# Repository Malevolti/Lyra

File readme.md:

*// Ingrediants //*

## Available from Mechboards ##
Pro-micro derivative x2 (except nice!nano right now) PUCHI-c or Elite-C Recommended (onboard reset switch)
0,91 oled x2
Trrs jacks x2- narrow (corne,lily style etc)
10 or 12mm standoffs x50
6mm M2 screws x100 (yeah I know...)
through hole diodes x70 (though buy 100)

## Elsewhere ##
Insulation tape
Hookup wire
Brass or Copper rods 1-3mm width (This is optional but saves some time using in place of hookup wire on the collumns)

Case & plates - I can print these for you on demand, I'm going to release them open source eventually so can give you the stls if you have access to a printer or someone closer to you than me

*// Main build instructions //*

Google QMK - Handwire for the general instructions on how to handwire but a brief overview is:

1. Solder a diode to one  switch pin in direction marked below; other end soldered to the row "bus"; you can use the diode legs to from the row bus as long as the diode module is in parallel to the row bus.
2. Solder hookup wire or brass/copper rod to the other switch pin in direction marked below to form the collumn "bus"; no special considarations needed other than to insulate the collumns from the rows, especially if you are using a bare brass/copper rod; this is where the insulation tape comes in.

           ^ = Collumn bus
           |
<-----+----------> = Row bus
      _    |
Diode=^    |
      | O  o = Switch pins
      o    |
           |
           v

3. Once you have completed the matrix (above and below) then hook the collumn and row busses to the controller using the below diagram for reference; you can hook up each collumn or row at any point along each.

Matrix & pro micro pinout:

Left side - flipped over-

    0-F4 1-F5 2-F6 3-F7 4-B1 5-B3 6-B2
0-D4 +----+----+----+----+----+----+
     |    |    |    |    |    |    |
1-C6 +----+----+----+----+----+----+
     |    |    |    |    |    |    |
2-D7 +----+----+----+----+----+----+
     |    |    |    |    |    |    |
3-E6 +----+----+----+----+----+----+
     |    |    |    |    |    |    |
4-B5 +----+----+----+----+----+----+

Right side - flipped over-

    6-B2 5-B3 4-B1 3-F7 2-F6 1-F5 0-F4
0-D4 +----+----+----+----+----+----+
     |    |    |    |    |    |    |
1-C6 +----+----+----+----+----+----+
     |    |    |    |    |    |    |
2-D7 +----+----+----+----+----+----+
     |    |    |    |    |    |    |
3-E6 +----+----+----+----+----+----+
     |    |    |    |    |    |    |
4-B5 +----+----+----+----+----+----+

4. Wiring up the OLED -
	This is as simple as matching the pins named on the OLED module with the pins of the same name on the microcontroller; the main thing to know however is that the OLED shares the VCC in with the TRRS jack; I normally strip a small section of insulation from the wire between the oled VCC & MCU VCC and then soldering the Trrs vcc onto that as the hole on the mcu can only take one wire. Alternatively you can wire the oled vcc to the trrs pin that you choose to use for vcc and then wire the TRRS to the vcc on the mcu.

5. Wiring up the TRRS - 
	Normally the easiest part of soldering a split pcb; sadly this is a little bit fiddly with the lyra.
	Ignoring the pin on the TRRS that sits alone from the other three, it doesnt matter which pins you use for each pin on the microcontroller as long as you use the same ones on each trrs jack. 
	The three pins on the microcontroller needed for the TRRS are RX(D2), GND(any) & VCC (See above for info on shared use with 
	I would recommend using longer lengths of wire than appears needed due to how close the TRRS jacks are to the required pins.

------

*// Firmware //*
[Coming soon]

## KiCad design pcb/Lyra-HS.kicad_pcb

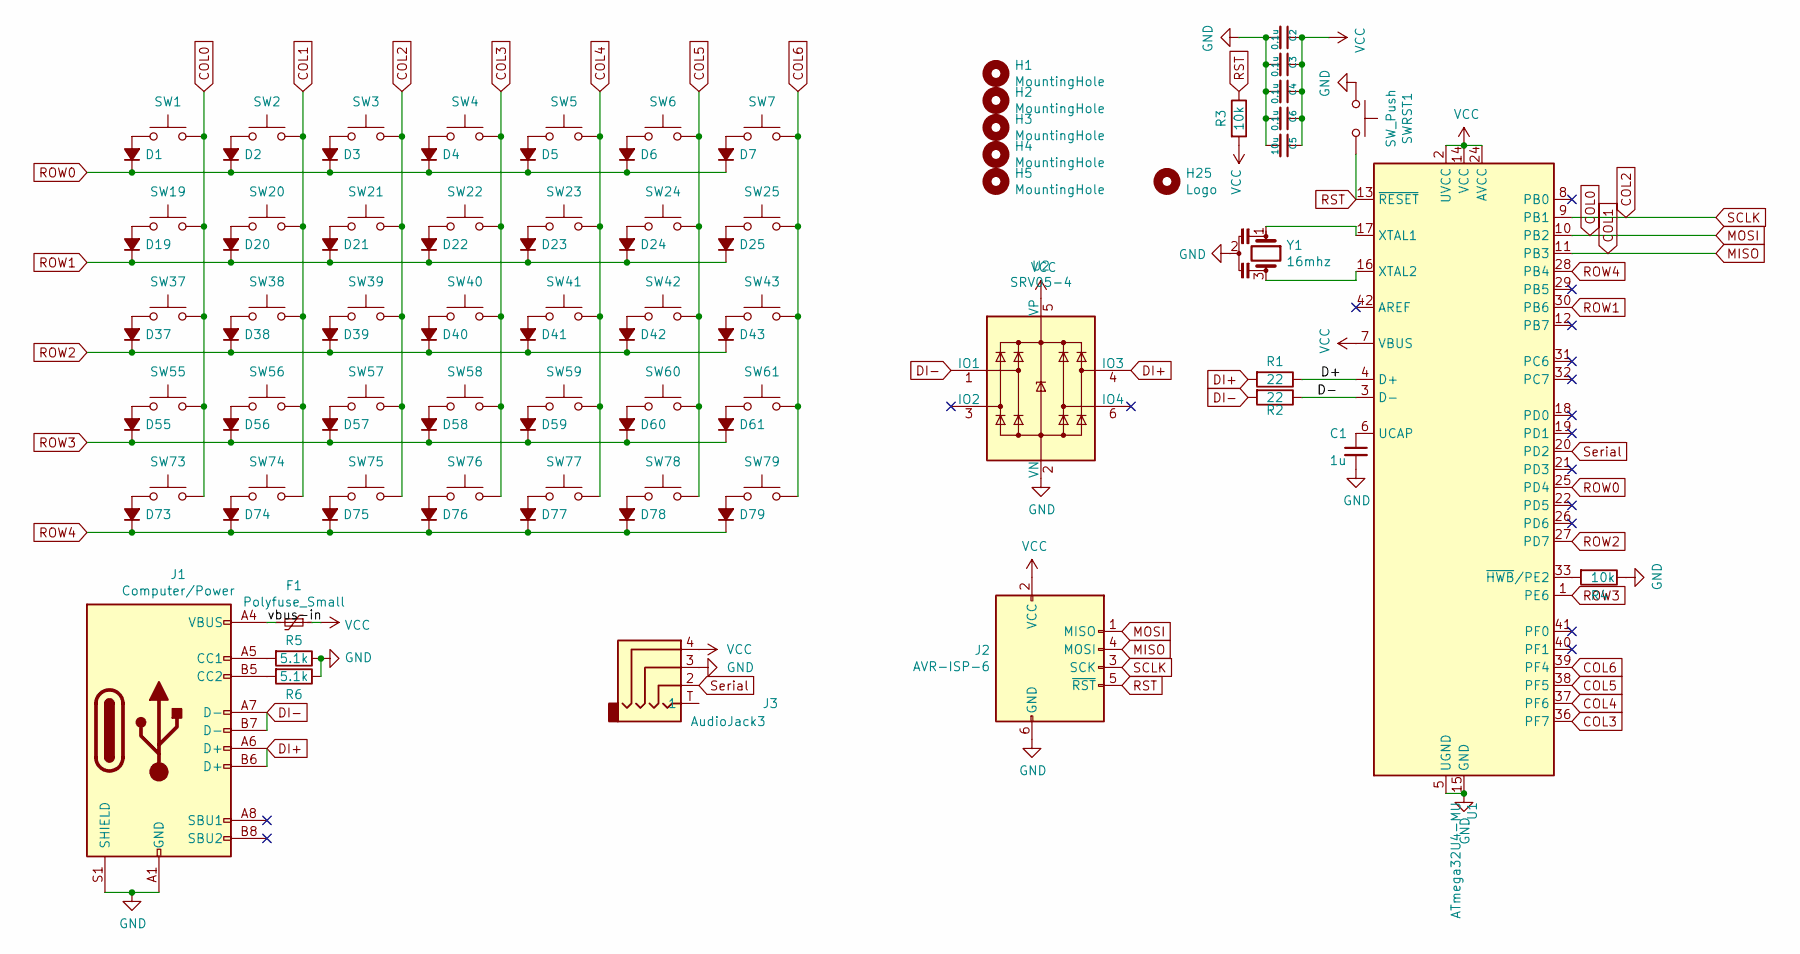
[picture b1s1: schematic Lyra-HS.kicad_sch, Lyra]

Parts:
C1: 1u; C_0402; LCSC C106253
C2, C3, C4, C6: 0.1u; C_0402; LCSC C106204
C5: 10u; C_0402; LCSC C237279
D1, D2, D3, D4, D5, D6, D7, D19, D20, D21, D22, D23, D24, D25, D37, D38, D39, D40, D41, D42, D43, D55, D56, D57, D58, D59, D60, D61, D73, D74, D75, D76, D77, D78, D79: D_Small_ALT; D_SOD-123F; LCSC C2099
F1: Polyfuse_Small; Fuse_0402_1005Metric; LCSC C914085
H1, H2, H3, H4, H5: MountingHole; MountingHole_2.2mm_M2_ISO7380_Pad
H25: Logo; SuperLyraLogo
J1: Computer/Power; USB_C_Receptacle_HRO_TYPE-C-31-M-12; LCSC C165948
J2: AVR-ISP-6; PinSocket_2x03_P2.54mm_Vertical
J3: AudioJack3; TRRS-PJ-320A-Dual-Overlayed
R1, R2: 22; R_0402_1005Metric_Pad0.72x0.64mm_HandSolder; LCSC C93929
R3, R4: 10k; R_0402_1005Metric_Pad0.72x0.64mm_HandSolder; LCSC C60489
R5, R6: 5.1k; R_0402_1005Metric_Pad0.72x0.64mm_HandSolder; LCSC C25905
SW1, SW2, SW3, SW4, SW5, SW6, SW7, SW19, SW20, SW21, SW22, SW23, SW24, SW25, SW37, SW38, SW39, SW40, SW41, SW42, SW43, SW55, SW56, SW57, SW58, SW59, SW60, SW61, SW73, SW74, SW75, SW76, SW77, SW78, SW79: SW_Push; MX_Choc_Hotswap
SWRST1: SW_Push; SW_SPST_TL3342; LCSC C318884
U1: ATmega32U4-MU; QFN-44-1EP_7x7mm_P0.5mm_EP5.2x5.2mm; LCSC C112161
U2: SRV05-4; SOT-23-6; LCSC C558418
Y1: 16mhz; Resonator_SMD_Murata_CSTxExxV-3Pin_3.0x1.1mm; LCSC C341521

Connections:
/D+: R1.1, U1.4 (D+)
/D-: R2.1, U1.3 (D-)
/vbus-in: F1.2, J1.A4 (VBUS), J1.A9 (VBUS), J1.B4 (VBUS), J1.B9 (VBUS)
COL0: J2.1 (MISO), SW1.2, SW19.2, SW37.2, SW55.2, SW73.2, U1.10 (PB2)
COL1: J2.4 (MOSI), SW2.2, SW20.2, SW38.2, SW56.2, SW74.2, U1.11 (PB3)
COL2: J2.3 (SCK), SW3.2, SW21.2, SW39.2, SW57.2, SW75.2, U1.9 (PB1)
COL3: SW4.2, SW22.2, SW40.2, SW58.2, SW76.2, U1.36 (PF7)
COL4: SW5.2, SW23.2, SW41.2, SW59.2, SW77.2, U1.37 (PF6)
COL5: SW6.2, SW24.2, SW42.2, SW60.2, SW78.2, U1.38 (PF5)
COL6: SW7.2, SW25.2, SW43.2, SW61.2, SW79.2, U1.39 (PF4)
DI+: J1.A6 (D+), J1.B6 (D+), R1.2, U2.4 (IO3)
DI-: J1.A7 (D-), J1.B7 (D-), R2.2, U2.1 (IO1)
GND: C1.2, C2.2, C3.2, C4.2, C5.2, C6.2, J1.A1 (GND), J1.A12 (GND), J1.B1 (GND), J1.B12 (GND), J1.S1 (SHIELD), J2.6 (GND), J3.3, R4.1, R5.1, R6.1, SWRST1.1, U1.5 (UGND), U1.15 (GND), U1.23 (GND), U1.35 (GND), U1.43 (GND), U1.45 (GND), U2.2 (VN), Y1.2
unnamed: C1.1, U1.6 (UCAP)
unnamed: D1.2 (A), SW1.1
unnamed: D2.2 (A), SW2.1
unnamed: D3.2 (A), SW3.1
unnamed: D4.2 (A), SW4.1
unnamed: D5.2 (A), SW5.1
unnamed: D6.2 (A), SW6.1
unnamed: D7.2 (A), SW7.1
unnamed: D19.2 (A), SW19.1
unnamed: D20.2 (A), SW20.1
unnamed: D21.2 (A), SW21.1
unnamed: D22.2 (A), SW22.1
unnamed: D23.2 (A), SW23.1
unnamed: D24.2 (A), SW24.1
unnamed: D25.2 (A), SW25.1
unnamed: D37.2 (A), SW37.1
unnamed: D38.2 (A), SW38.1
unnamed: D39.2 (A), SW39.1
unnamed: D40.2 (A), SW40.1
unnamed: D41.2 (A), SW41.1
unnamed: D42.2 (A), SW42.1
unnamed: D43.2 (A), SW43.1
unnamed: D55.2 (A), SW55.1
unnamed: D56.2 (A), SW56.1
unnamed: D57.2 (A), SW57.1
unnamed: D58.2 (A), SW58.1
unnamed: D59.2 (A), SW59.1
unnamed: D60.2 (A), SW60.1
unnamed: D61.2 (A), SW61.1
unnamed: D73.2 (A), SW73.1
unnamed: D74.2 (A), SW74.1
unnamed: D75.2 (A), SW75.1
unnamed: D76.2 (A), SW76.1
unnamed: D77.2 (A), SW77.1
unnamed: D78.2 (A), SW78.1
unnamed: D79.2 (A), SW79.1
unnamed: J1.A5 (CC1), R5.2
unnamed: J1.B5 (CC2), R6.2
unnamed: R4.2, U1.33 (~HWB/PE2)
unnamed: U1.16 (XTAL2), Y1.3
unnamed: U1.17 (XTAL1), Y1.1
ROW0: D1.1 (K), D2.1 (K), D3.1 (K), D4.1 (K), D5.1 (K), D6.1 (K), D7.1 (K), U1.25 (PD4)
ROW1: D19.1 (K), D20.1 (K), D21.1 (K), D22.1 (K), D23.1 (K), D24.1 (K), D25.1 (K), U1.30 (PB6)
ROW2: D37.1 (K), D38.1 (K), D39.1 (K), D40.1 (K), D41.1 (K), D42.1 (K), D43.1 (K), U1.27 (PD7)
ROW3: D55.1 (K), D56.1 (K), D57.1 (K), D58.1 (K), D59.1 (K), D60.1 (K), D61.1 (K), U1.1 (PE6)
ROW4: D73.1 (K), D74.1 (K), D75.1 (K), D76.1 (K), D77.1 (K), D78.1 (K), D79.1 (K), U1.28 (PB4)
RST: J2.5 (~RST), R3.1, SWRST1.2, U1.13 (~RESET)
Serial: J3.2, U1.20 (PD2)
VCC: C2.1, C3.1, C4.1, C5.1, C6.1, F1.1, J2.2 (VCC), J3.4, R3.2, U1.2 (UVCC), U1.7 (VBUS), U1.14 (VCC), U1.24 (AVCC), U1.34 (VCC), U1.44 (AVCC), U2.5 (VP)

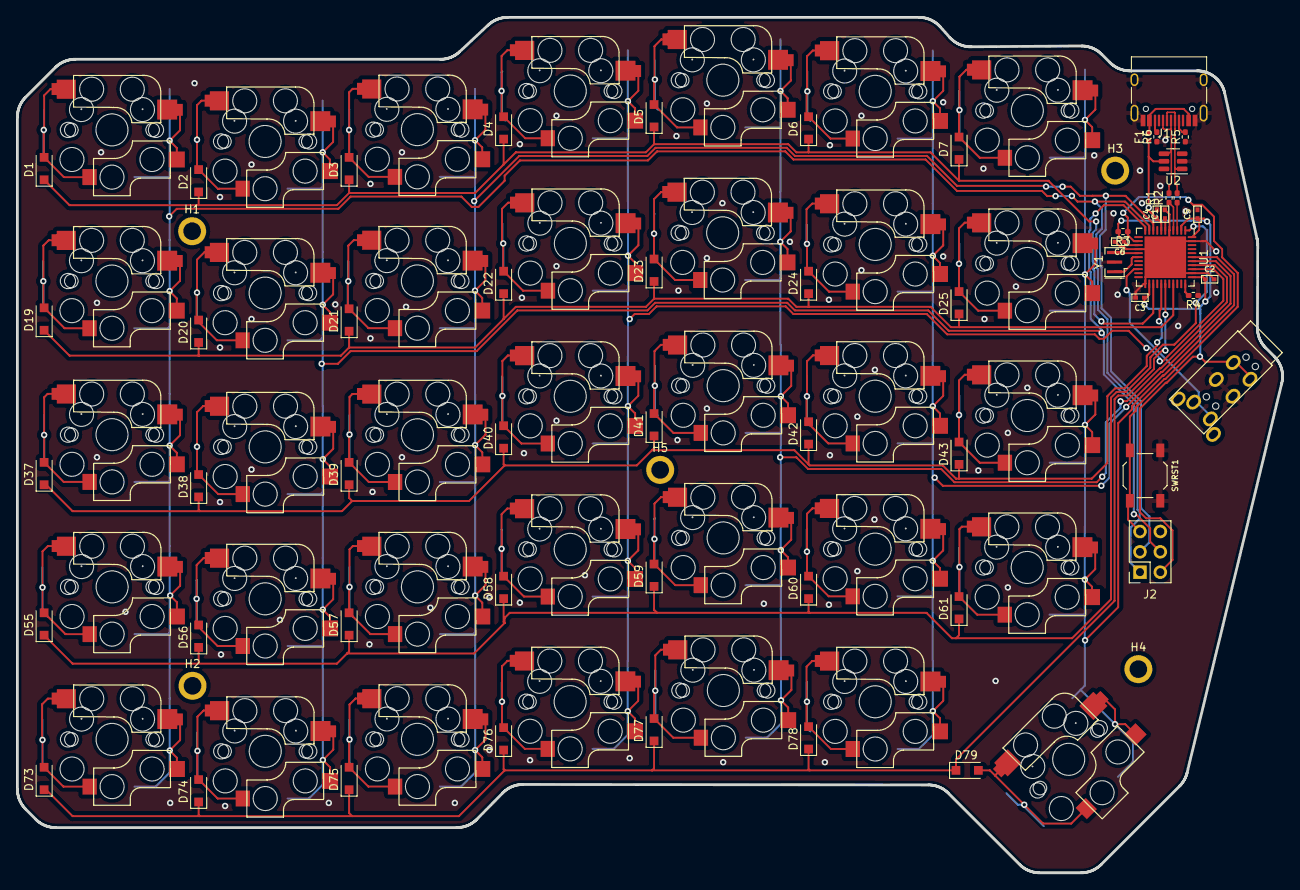
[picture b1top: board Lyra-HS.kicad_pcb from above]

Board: 2 copper layers, 158.1 x 106.9 mm, 95 parts (0 on the bottom side), 62 nets.

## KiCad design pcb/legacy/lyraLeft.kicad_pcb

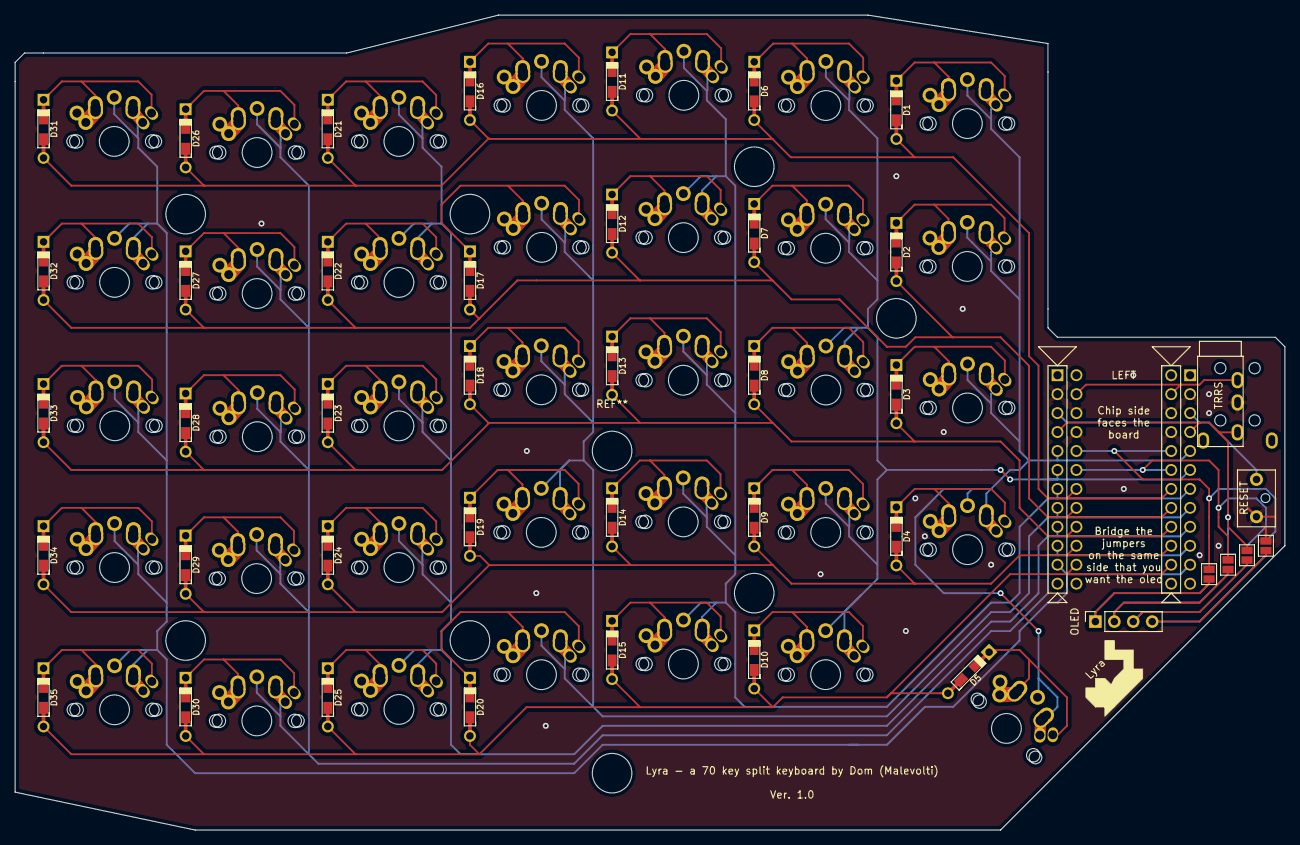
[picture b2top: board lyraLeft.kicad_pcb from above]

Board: 2 copper layers, 170.2 x 109.2 mm, 73 parts (0 on the bottom side), 55 nets.

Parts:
D1, D2, D3, D4, D5, D6, D7, D8, D9, D10, D11, D12, D13, D14, D15, D16, D17, D18, D19, D20, D21, D22, D23, D24, D25, D26, D27, D28, D29, D30, D31, D32, D33, D34, D35: DIODE; Diode-dual
OLED: PinSocket_1x04_P2.54mm_Vertical
RESET: SW_PUSH; SW_Tactile_SPST_Angled_MJTP1117-no-mount
SW1: SW_SPST; Triple-Dual-1u-NOLED
SW2, SW3, SW4, SW5, SW6, SW7, SW8, SW9, SW10, SW11, SW12, SW13, SW14, SW15, SW16, SW17, SW18, SW19, SW20, SW21, SW22, SW23, SW24, SW25, SW26, SW27, SW28, SW29, SW30, SW31, SW32, SW33, SW34, SW35: SW_SPST; Triple-Dual-1u-LED
U1: ATmega32U4-MU; ProMicro

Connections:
Earth: RESET.2, U1.2, U1.21, U1.22
unnamed: D1.1, SW1.1
unnamed: D1.2, D6.2, D11.2, D16.2, D21.2, D26.2, D31.2
unnamed: D2.1, SW2.1
unnamed: D3.1, SW3.1
unnamed: D4.1, SW4.1
unnamed: D5.1, SW5.1
unnamed: D6.1, SW6.1
unnamed: D7.1, SW7.1
unnamed: D8.1, SW8.1
unnamed: D9.1, SW9.1
unnamed: D10.1, SW10.1
unnamed: D5.2, D10.2, D15.2, D20.2, D25.2, D30.2, D35.2
unnamed: D11.1, SW11.1
unnamed: D12.1, SW12.1
unnamed: D2.2, D7.2, D12.2, D17.2, D22.2, D27.2, D32.2
unnamed: D13.1, SW13.1
unnamed: D3.2, D8.2, D13.2, D18.2, D23.2, D28.2, D33.2
unnamed: D14.1, SW14.1
unnamed: D4.2, D9.2, D14.2, D19.2, D24.2, D29.2, D34.2
unnamed: D15.1, SW15.1
unnamed: D16.1, SW16.1
unnamed: D17.1, SW17.1
unnamed: D18.1, SW18.1
unnamed: D19.1, SW19.1
unnamed: D20.1, SW20.1
unnamed: D21.1, SW21.1
unnamed: D22.1, SW22.1
unnamed: D23.1, SW23.1
unnamed: D24.1, SW24.1
unnamed: D25.1, SW25.1
unnamed: D26.1, SW26.1
unnamed: D27.1, SW27.1
unnamed: D28.1, SW28.1
unnamed: D29.1, SW29.1
unnamed: D30.1, SW30.1
unnamed: D31.1, SW31.1
unnamed: D32.1, SW32.1
unnamed: D33.1, SW33.1
unnamed: D34.1, SW34.1
unnamed: D35.1, SW35.1
unnamed: RESET.1, U1.3
unnamed: SW1.2, SW2.2, SW3.2, SW4.2, SW5.2
unnamed: SW6.2, SW7.2, SW8.2, SW9.2, SW10.2
unnamed: SW11.2, SW12.2, SW13.2, SW14.2, SW15.2
unnamed: SW16.2, SW17.2, SW18.2, SW19.2, SW20.2
unnamed: SW21.2, SW22.2, SW23.2, SW24.2, SW25.2
unnamed: SW26.2, SW27.2, SW28.2, SW29.2, SW30.2, U1.11
unnamed: SW31.2, SW32.2, SW33.2, SW34.2, SW35.2, U1.10
unnamed: U1.23, U1.24
unnamed: U1.5, U1.17
unnamed: U1.6, U1.16
unnamed: U1.7, U1.15
unnamed: U1.8, U1.14
unnamed: U1.9, U1.13

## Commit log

2021-07-25 initial
2021-08-12 add pcb
2021-08-30 add case files
2021-08-30 update ULP case
    Better pcb support, some mount points made passive due to no clearance between switch & lug
2022-01-23 Initial 'R2G' schem
2022-01-23 Initial PCB
    (Super alpha, basically no traces)
2022-01-24 Initial matrix layout
2022-01-24 Initial MCU>Matrix hookup
2022-01-24 Initial Edge Cuts
2022-01-25 MCU area shenanigans
2022-01-26 Matrix impedance optimisations
    +change to desolder-friendly trrs jack footprint
2022-01-26 edge cut changes
    empty space removed below MCU/TRRS
2022-01-28 Changed USB-C port from Top-mount to Mid-mount
2022-01-29 Misc tidying
2022-01-29 moar misc tidying
